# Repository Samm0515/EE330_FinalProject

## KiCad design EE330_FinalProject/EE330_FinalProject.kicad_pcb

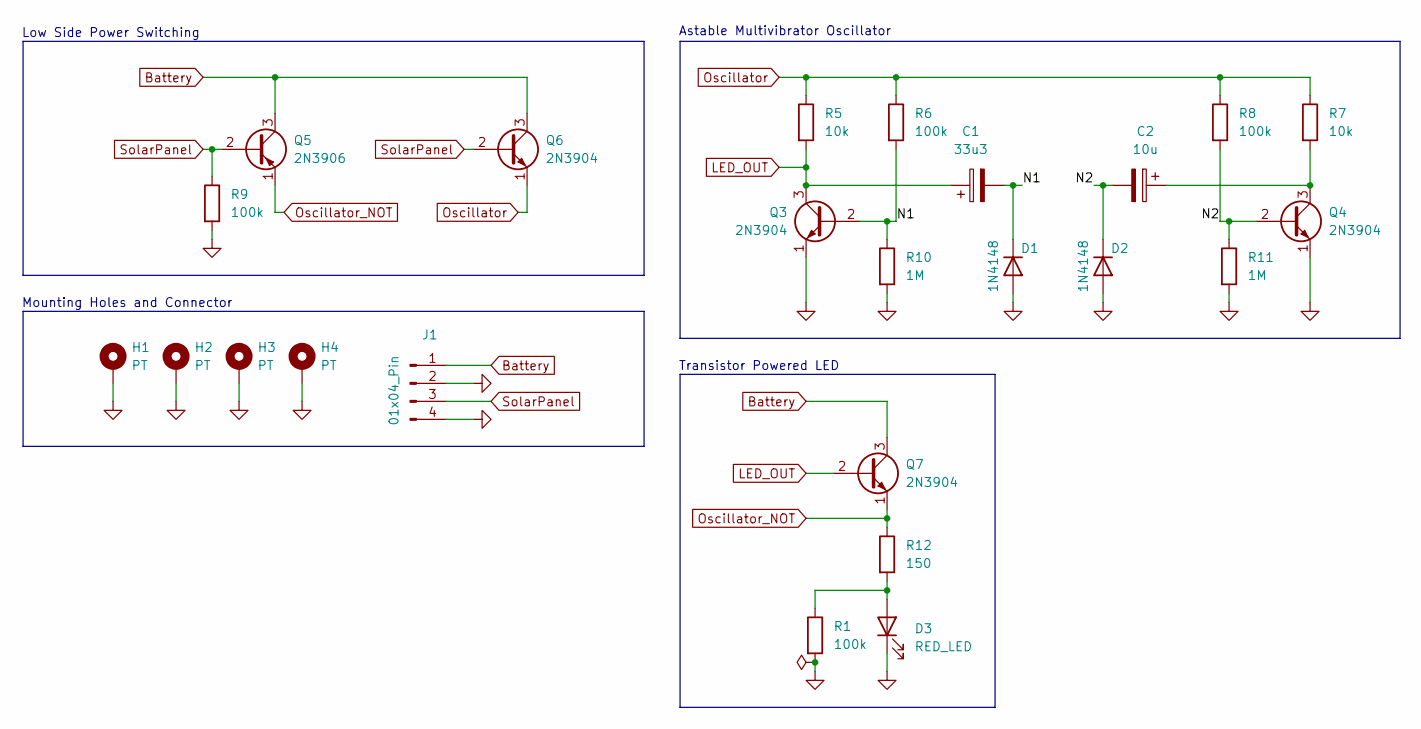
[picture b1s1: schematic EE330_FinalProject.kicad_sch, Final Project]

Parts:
C1: 33u3; C_0805_2012Metric
C2: 10u; C_0805_2012Metric
D1, D2: 1N4148; D_DO-35_SOD27_P7.62mm_Horizontal
D3: RED_LED; LED_0805_2012Metric
H1, H2, H3, H4: PT; MountingHole_3.2mm_M3_DIN965_Pad_TopBottom
J1: 01x04_Pin; PinHeader_1x04_P1.27mm_Vertical
Q3, Q4, Q6, Q7: 2N3904; TO-92_Inline
Q5: 2N3906; TO-92_Inline
R1, R6, R8, R9: 100k; R_0603_1608Metric
R5, R7: 10k; R_0603_1608Metric
R10, R11: 1M; R_0603_1608Metric
R12: 150; R_0603_1608Metric

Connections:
/N1: C1.2, D1.1 (K), Q3.2 (B), R6.2, R10.1
/N2: C2.2, D2.1 (K), Q4.2 (B), R8.2, R11.1
Battery: J1.1, Q5.3 (C), Q6.3 (C), Q7.3 (C)
GND: D1.2 (A), D2.2 (A), D3.1 (K), H1.1, H2.1, H3.1, H4.1, J1.2, J1.4, Q3.1 (E), Q4.1 (E), R1.2, R9.2, R10.2, R11.2
LED_OUT: C1.1, Q3.3 (C), Q7.2 (B), R5.2
unnamed: D3.2 (A), R1.1, R12.2
unnamed: C2.1, Q4.3 (C), R7.2
Oscillator: Q6.1 (E), R5.1, R6.1, R7.1, R8.1
Oscillator_NOT: Q5.1 (E), Q7.1 (E), R12.1
SolarPanel: J1.3, Q5.2 (B), Q6.2 (B), R9.1

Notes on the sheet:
Low Side Power Switching
Mounting Holes and Connector
Transistor Powered LED
Astable Multivibrator Oscillator

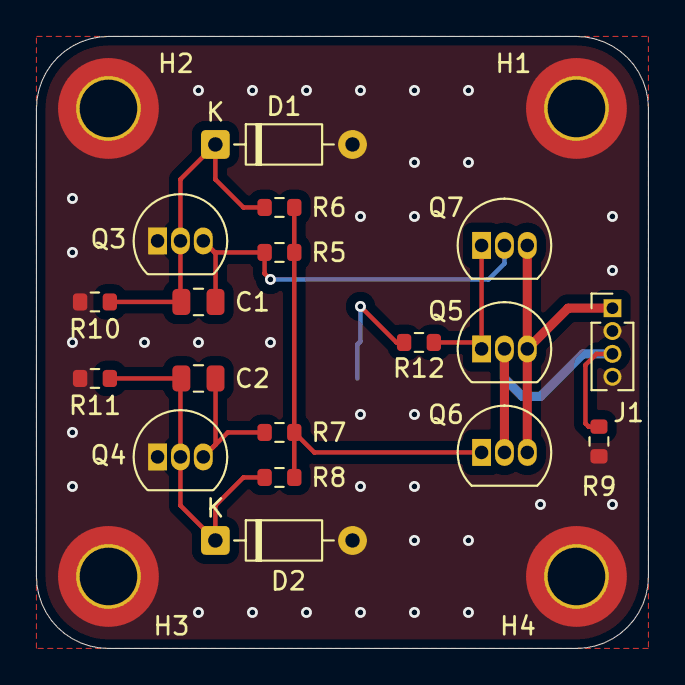
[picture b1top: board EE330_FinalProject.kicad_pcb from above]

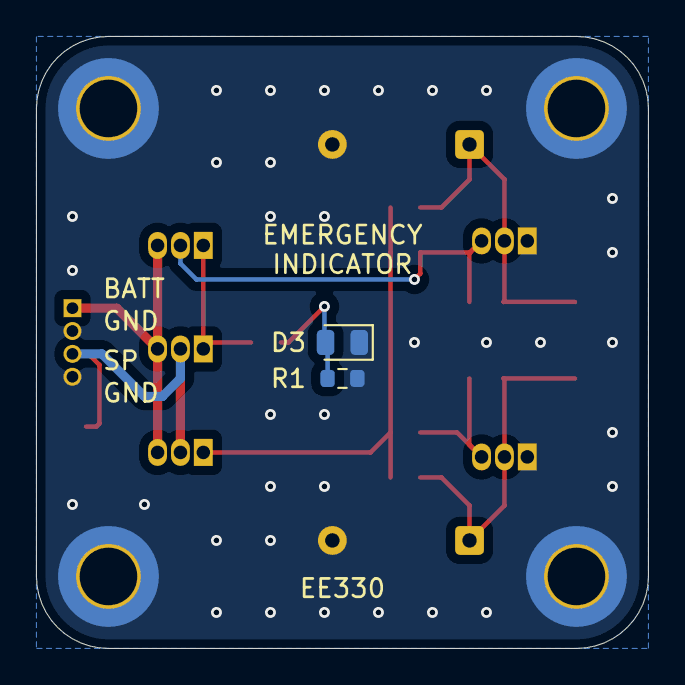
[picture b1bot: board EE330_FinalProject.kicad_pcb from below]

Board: 2 copper layers, 34.0 x 34.0 mm, 24 parts (2 on the bottom side), 10 nets.

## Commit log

2025-11-19 Worked on schematic added astable multivibrator, mounting holes and connector
2025-11-19 Updated PCB with component footprints and started Board design
2025-11-19 Cleaned up schematic and ran DRC
2025-11-20 Updated schematic based on working design
2025-11-20 Updated schematic and PCB based on the testing done today. Need to confirm physical setup before finalizing
2025-11-21 Finished PCB Design with layout and routing
